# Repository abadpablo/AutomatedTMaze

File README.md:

# AutomatedTMaze

Welcome to the AutomatedTMaze repository !! This is a repository for having all the necessary elements for building an automated TMaze (3D print files and PCB files).

In the Blender files folder you can find the original Blender files in case you want to edit them.

In the Stl files folder you can find the STL files ready for printing in a filament 3D printer machine.

In the Autodesk fusion files you can find the Eagle/Autodesk fusion files. Inside it there is a .zip folder ("Maze.zip") that is the one you want to upload into the PCBway webpage (https://www.pcbway.es/) for fabrication.

## Components

1. Arduino Nano
2. 100 uF capacitor (x7)
3. Servomotor (x5)
4. PCB screw terminals 2 pins (x5)
5. PCB screw terminals 3 pins (x9)
6. PCB screw terminals 4 pins (x1)
7. Mosfet N-terminal IRF520N (x2)
8. IR sensor (x4)

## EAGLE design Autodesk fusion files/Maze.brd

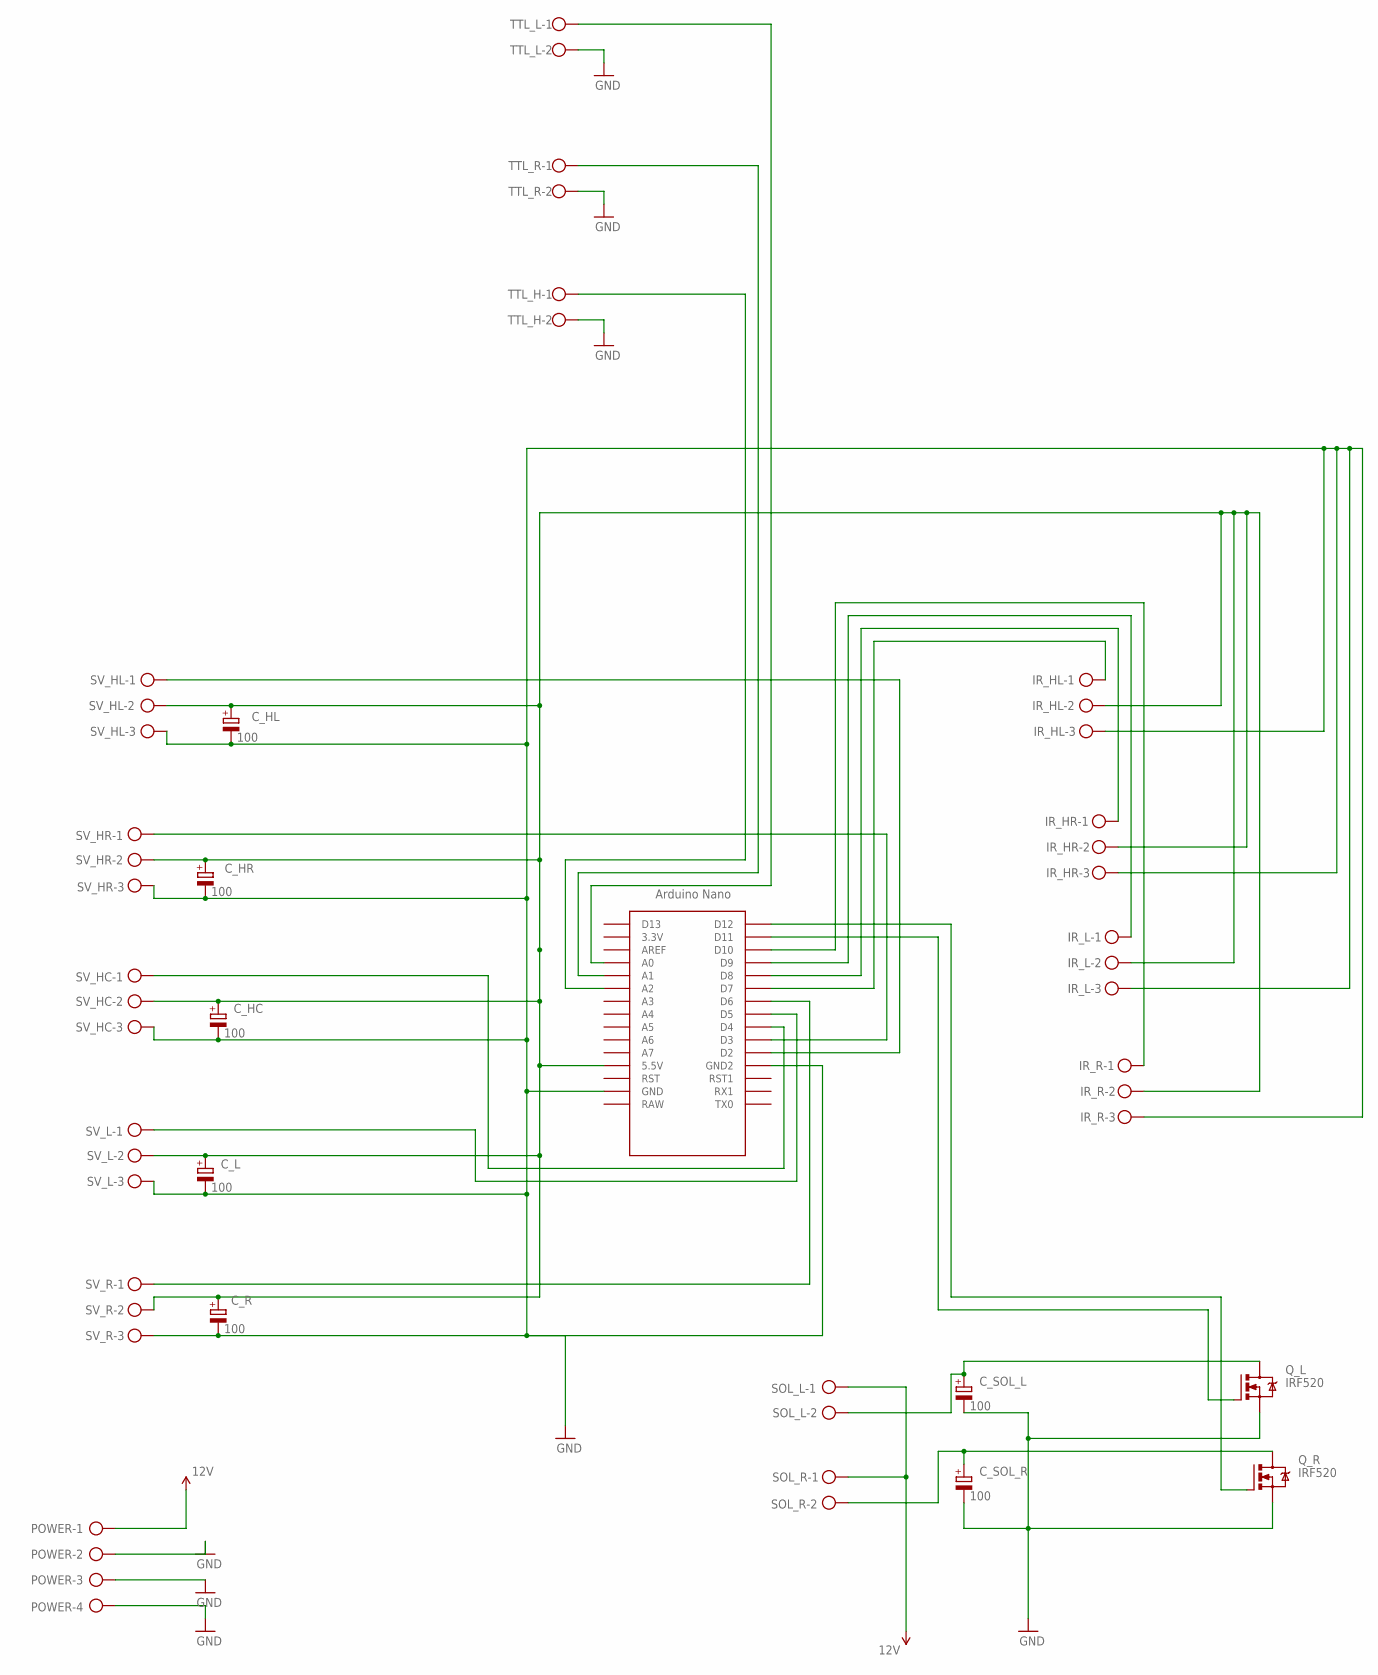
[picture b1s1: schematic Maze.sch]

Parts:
C_HC: 100; E2,5-6
C_HL: 100; E2,5-6
C_HR: 100; E2,5-6
C_L: 100; E2,5-6
C_R: 100; E2,5-6
C_SOL_L: 100; E2,5-6
C_SOL_R: 100; E2,5-6
IR_HL: W237-103
IR_HR: W237-103
IR_L: W237-103
IR_R: W237-103
POWER: W237-4
Q_L: IRF520; TO220BV
Q_R: IRF520; TO220BV
SOL_L: W237-102
SOL_R: W237-102
SV_HC: W237-103
SV_HL: W237-103
SV_HR: W237-103
SV_L: W237-103
SV_R: W237-103
TTL_H: W237-102
TTL_L: W237-102
TTL_R: W237-102
U$1: NANO

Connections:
12V: POWER.1, SOL_L.1, SOL_R.1
GND: C_HC.-, C_HL.-, C_HR.-, C_L.-, C_R.-, C_SOL_L.-, C_SOL_R.-, IR_HL.3, IR_HR.3, IR_L.3, IR_R.3, POWER.2, POWER.3, POWER.4, Q_L.S, Q_R.S, SV_HC.3, SV_HL.3, SV_HR.3, SV_L.3, SV_R.3, TTL_H.2, TTL_L.2, TTL_R.2, U$1.GND, U$1.GND1 (GND2)
unnamed: SV_HL.1, U$1.D2
unnamed: SV_HC.1, U$1.D4
unnamed: SV_R.1, U$1.D6
unnamed: SV_HR.1, U$1.D3
unnamed: SV_L.1, U$1.D5
unnamed: IR_HL.1, U$1.D7
unnamed: C_HC.+, C_HL.+, C_HR.+, C_L.+, C_R.+, IR_HL.2, IR_HR.2, IR_L.2, IR_R.2, SV_HC.2, SV_HL.2, SV_HR.2, SV_L.2, SV_R.2, U$1.5V (5.5V)
unnamed: IR_HR.1, U$1.D8
unnamed: IR_L.1, U$1.D9
unnamed: IR_R.1, U$1.D10
unnamed: C_SOL_L.+, Q_L.D, SOL_L.2
unnamed: Q_L.G, U$1.D11
unnamed: C_SOL_R.+, Q_R.D, SOL_R.2
unnamed: Q_R.G, U$1.D12
unnamed: TTL_L.1, U$1.A0
unnamed: TTL_R.1, U$1.A1
unnamed: TTL_H.1, U$1.A2

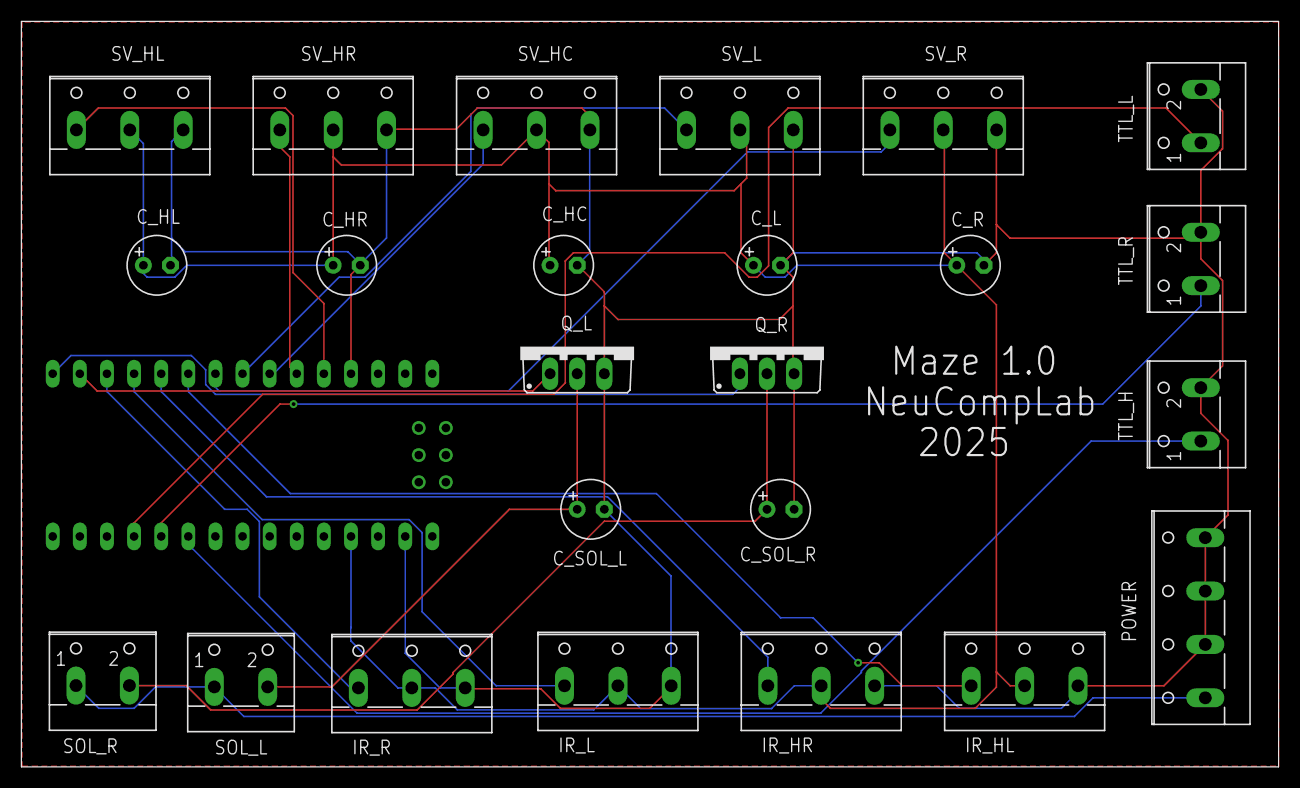
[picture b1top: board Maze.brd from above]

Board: 2 copper layers, 117.8 x 69.8 mm, 25 parts (0 on the bottom side), 19 nets.

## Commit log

2026-02-18 Added files

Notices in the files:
parts and their libraries:
SparkFun-PowerSymbols: Licensing: Creative Commons ShareAlike 4.0 International - https://creativecommons.org/licenses/by-sa/4.0
